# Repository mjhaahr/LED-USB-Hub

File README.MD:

# 3-Port USB Hub with Integrated Microcontroller and RGB USB-A ports

V1 uses the SL2.1a USB Hub
V2 will switch to a more full-featured USB Hub Controller and more closely comply with the USB Spec

Features:
- 3x RGB LED USB (USB A, 2.0 Speed) ports
- 1x USB C Port (downstream)
- 1x RP 2040
  - V1 used an Adafruit KB2040
  - V2 will switch to a standalone implementation
- Possibly exposed connectors for more features externally or internally (i.e. leaving a cutout in the board with room for expansion)

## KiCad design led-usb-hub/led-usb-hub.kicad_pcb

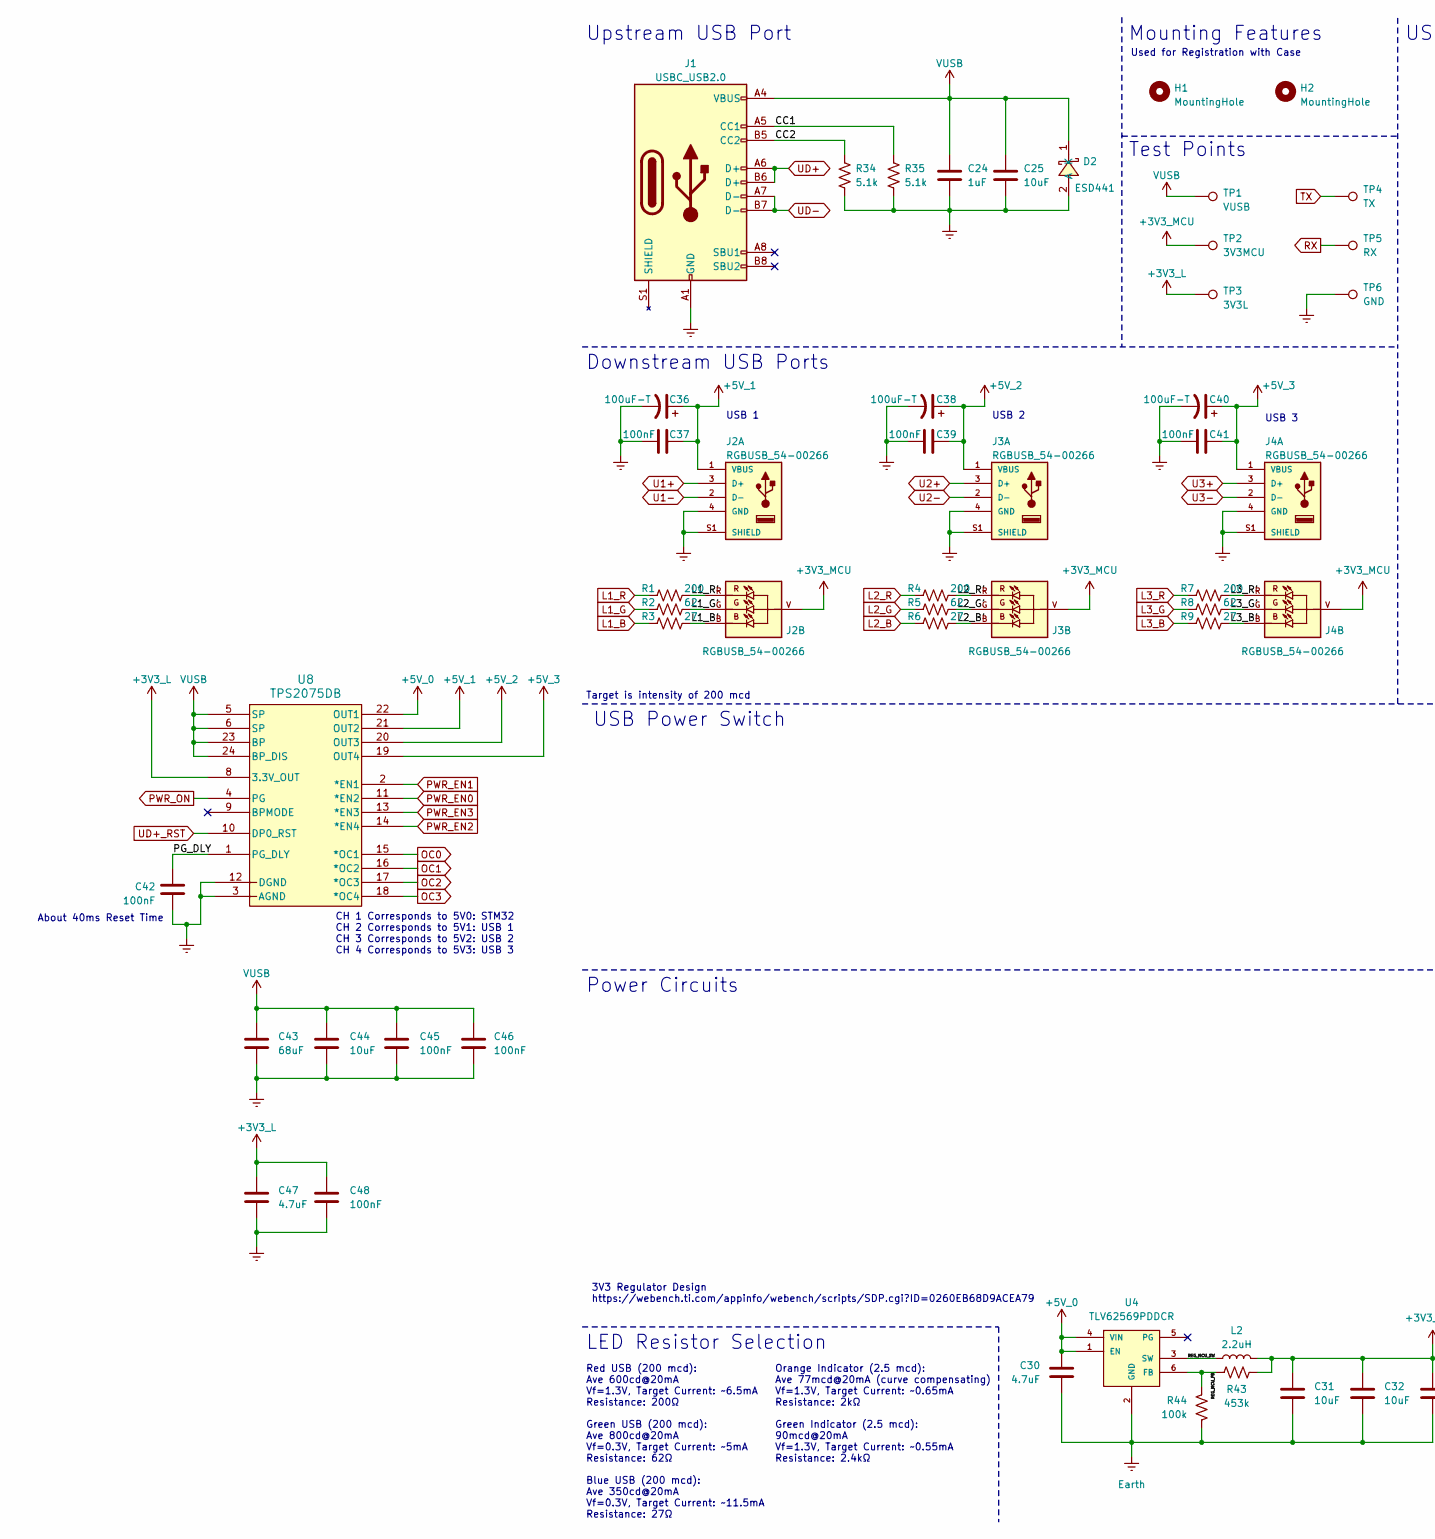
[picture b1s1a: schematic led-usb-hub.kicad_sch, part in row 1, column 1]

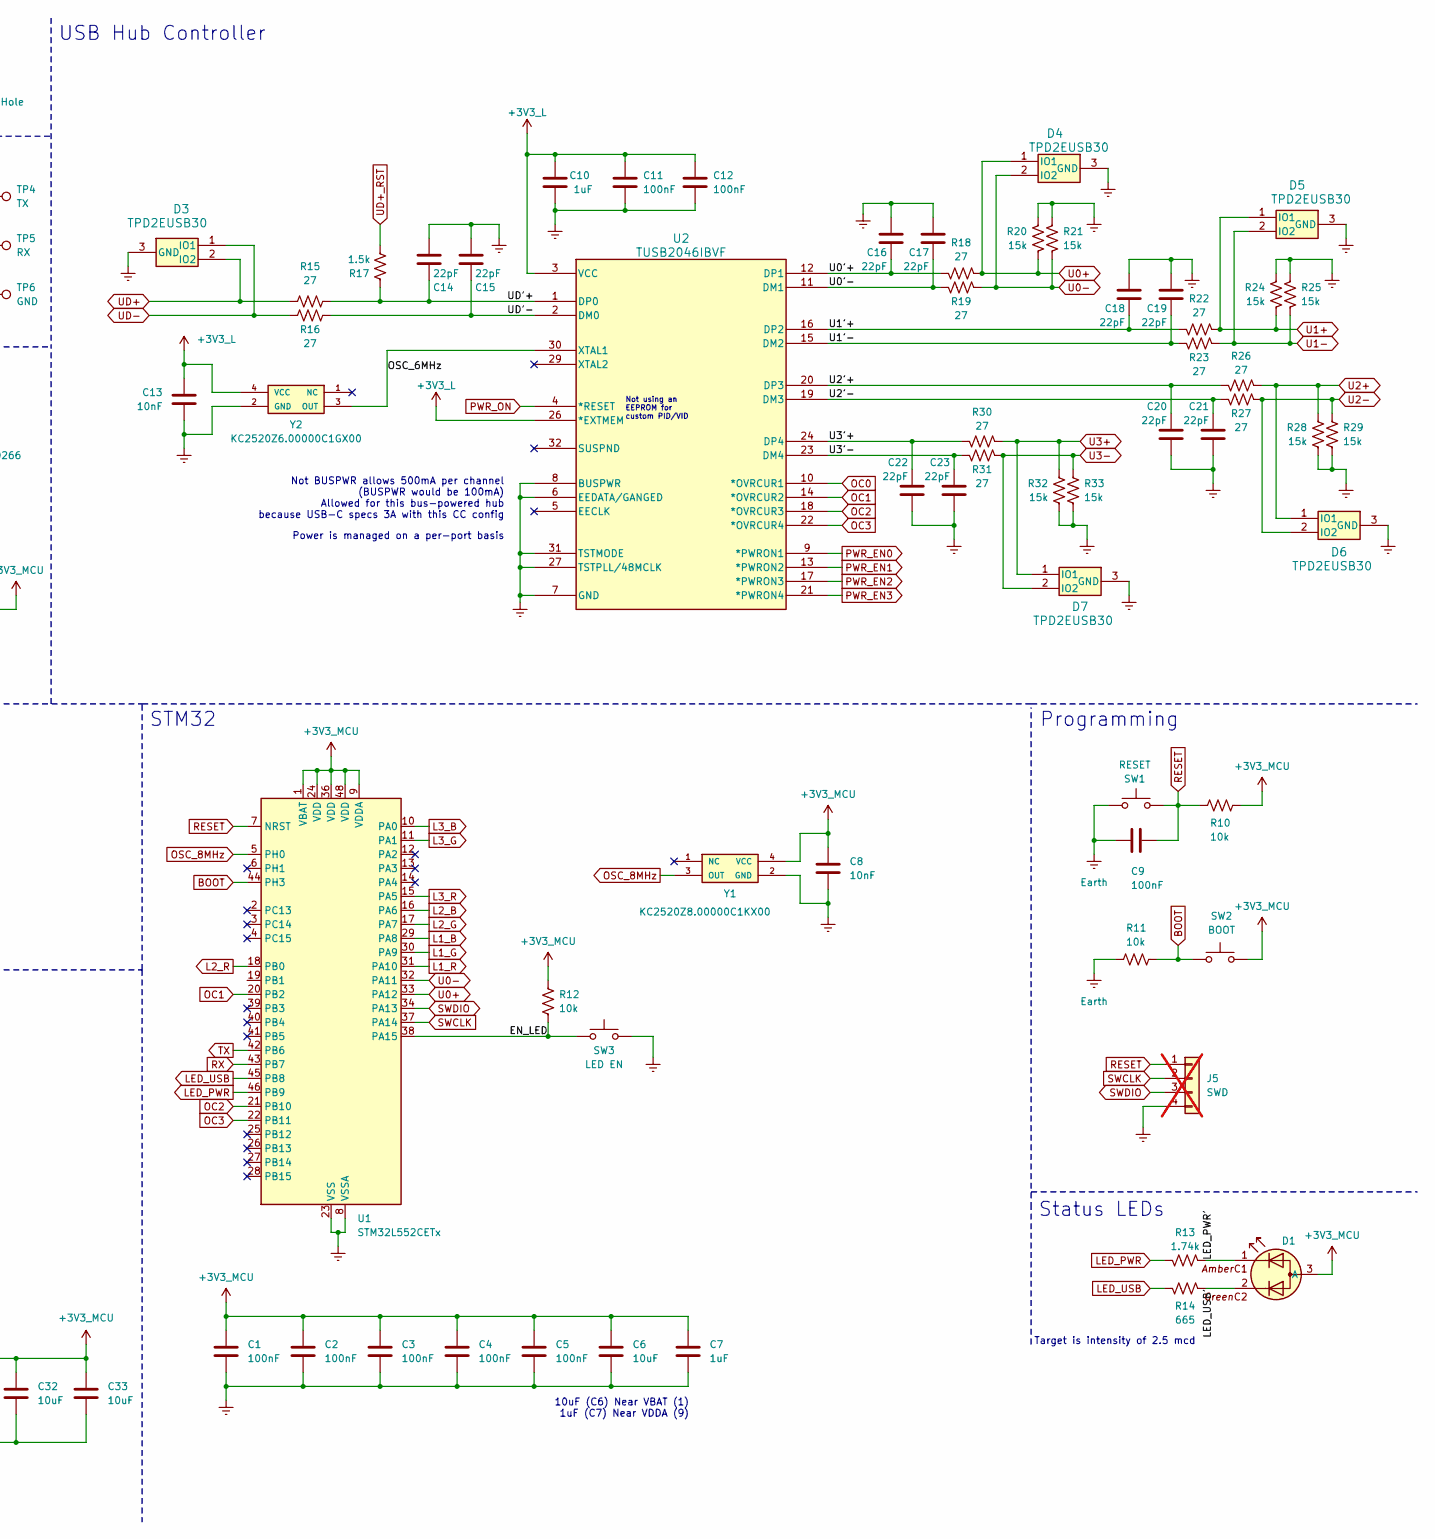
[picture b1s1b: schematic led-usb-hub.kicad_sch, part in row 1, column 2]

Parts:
C1, C2, C3, C4, C5, C9: 100nF; C_0603_1608Metric; LCSC Part C7472949
C6: 10uF; C_0603_1608Metric; LCSC Part C7472949
C7: 1uF; C_0603_1608Metric; LCSC Part C7472949
C8, C13: 10nF; C_0603_1608Metric; LCSC Part C7472949
C10, C24: 1uF; C_0603_1608Metric
C11, C12, C37, C39, C41, C42, C45, C46, C48: 100nF; C_0603_1608Metric
C14, C15, C16, C17, C18, C19, C20, C21, C22, C23: 22pF; C_0603_1608Metric
C25, C31, C32, C33, C44: 10uF; C_0603_1608Metric
C30, C47: 4.7uF; C_0603_1608Metric
C36, C38, C40: 100uF-T; CP_EIA-3528-15_AVX-H
C43: 68uF; C_0603_1608Metric
D1: HSMF-C143
D2: ESD441; X2SON-2_L0.6-W0.3-P0.35_ESD441DPLR; LCSC Part C22427765
D3, D4, D5, D6, D7: TPD2EUSB30; DRT0003A
H1, H2: MountingHole; MountingHole_2mm
J1: USBC_USB2.0; USB_C_Receptacle_GCT_USB4085
J2, J3, J4: RGBUSB_54-00266; PARTREV A; DigiKey_Part_Number 839-54-00266TR-ND
J5: SWD; PinHeader_1x04_P2.54mm_Vertical; not fitted
L2: 2.2uH; IND_SRP4020FA-2R2M_BRN
R1, R4, R7: 200; R_0603_1608Metric
R2, R5, R8: 62; R_0603_1608Metric
R3, R6, R9, R15, R16, R18, R19, R22, R23, R26, R27, R30, R31: 27; R_0603_1608Metric
R10, R11, R12: 10k; R_0603_1608Metric
R13: 1.74k; R_0603_1608Metric
R14: 665; R_0603_1608Metric
R17: 1.5k; R_0603_1608Metric
R20, R21, R24, R25, R28, R29, R32, R33: 15k; R_0603_1608Metric
R34, R35: 5.1k; R_0603_1608Metric
R43: 453k; R_0603_1608Metric
R44: 100k; R_0603_1608Metric
SW1: RESET; SW_EVQ-P7L01P
SW2: BOOT; SW_EVQ-P7L01P
SW3: LED EN; SW_EVQ-P7L01P
TP1: VUSB; TestPoint_Pad_1.0x1.0mm_Mod
TP2: 3V3MCU; TestPoint_Pad_1.0x1.0mm_Mod
TP3: 3V3L; TestPoint_Pad_1.0x1.0mm_Mod
TP4: TX; TestPoint_Pad_1.0x1.0mm_Mod
TP5: RX; TestPoint_Pad_1.0x1.0mm_Mod
TP6: GND; TestPoint_Pad_1.0x1.0mm_Mod
U1: STM32L552CETx; LQFP-48_7x7mm_P0.5mm
U2: TUSB2046IBVF; LQFP-32_7x7mm_P0.8mm
U4: TLV62569PDDCR; SOT95P280X110-6N
U8: TPS2075DB; SSOP-24_5.3x8.2mm_P0.65mm
Y1: KC2520Z8.00000C1KX00; OSC_KC2520Z8.00000C1KX00; PARTREV October 16, 2023
Y2: KC2520Z6.00000C1GX00; OSC_KC2520Z6.00000C1GX00; PARTREV October 16, 2023; DigiKey_Part_Number 478-KC2520Z6.00000C1GX00TR-ND

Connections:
+3V3_L: C10.1, C11.1, C12.1, C13.1, C47.1, C48.1, TP3.1, U2.3 (VCC), U2.25 (VCC), U2.26 (*EXTMEM), U8.8 (3.3V_OUT), Y2.4 (VCC)
+3V3_MCU: C1.1, C2.1, C3.1, C4.1, C5.1, C6.1, C7.1, C8.1, C31.1, C32.1, C33.1, D1.3 (A), J2.V, J3.V, J4.V, L2.2, R10.2, R12.1, R43.1, SW2.1, TP2.1, U1.1 (VBAT), U1.9 (VDDA), U1.24 (VDD), U1.36 (VDD), U1.48 (VDD), Y1.4 (VCC)
+5V_0: C30.1, U4.1 (EN), U4.4 (VIN), U8.22 (OUT1)
+5V_1: C36.1, C37.1, J2.1 (VBUS), U8.21 (OUT2)
+5V_2: C38.1, C39.1, J3.1 (VBUS), U8.20 (OUT3)
+5V_3: C40.1, C41.1, J4.1 (VBUS), U8.19 (OUT4)
/CC1: J1.A5 (CC1), R35.2
/CC2: J1.B5 (CC2), R34.2
/EN_LED: R12.2, SW3.1, U1.38 (PA15)
/L1_B': J2.B, R3.2
/L1_G': J2.G, R2.2
/L1_R': J2.R, R1.2
/L2_B': J3.B, R6.2
/L2_G': J3.G, R5.2
/L2_R': J3.R, R4.2
/L3_B': J4.B, R9.2
/L3_G': J4.G, R8.2
/L3_R': J4.R, R7.2
/LED_PWR': D1.1, R13.2
/LED_USB': D1.2, R14.2
/OSC_6MHz: U2.30 (XTAL1), Y2.3 (OUT)
/PG_DLY: C42.2, U8.1 (PG_DLY)
/REG_MCU_FB: R43.2, R44.2, U4.6 (FB)
/REG_MCU_SW: L2.1, U4.3 (SW)
/U0'+: C16.1, R18.1, U2.12 (DP1)
/U0'-: C17.1, R19.1, U2.11 (DM1)
/U1'+: C18.1, R22.1, U2.16 (DP2)
/U1'-: C19.1, R23.1, U2.15 (DM2)
/U2'+: C20.1, R26.1, U2.20 (DP3)
/U2'-: C21.1, R27.1, U2.19 (DM3)
/U3'+: C22.1, R30.1, U2.24 (DP4)
/U3'-: C23.1, R31.1, U2.23 (DM4)
/UD'+: C14.1, R15.1, R17.2, U2.1 (DP0)
/UD'-: C15.1, R16.1, U2.2 (DM0)
BOOT: R11.1, SW2.2, U1.44 (PH3)
Earth: C1.2, C2.2, C3.2, C4.2, C5.2, C6.2, C7.2, C8.2, C9.2, C10.2, C11.2, C12.2, C13.2, C14.2, C15.2, C16.2, C17.2, C18.2, C19.2, C20.2, C21.2, C22.2, C23.2, C24.2, C25.2, C30.2, C31.2, C32.2, C33.2, C36.2, C37.2, C38.2, C39.2, C40.2, C41.2, C42.1, C43.2, C44.2, C45.2, C46.2, C47.2, C48.2, D2.2 (A), D3.3 (GND), D4.3 (GND), D5.3 (GND), D6.3 (GND), D7.3 (GND), J1.A1 (GND), J1.A12 (GND), J1.B1 (GND), J1.B12 (GND), J2.4 (GND), J2.S1 (SHIELD), J2.S2 (SHIELD), J2.S3 (SHIELD), J2.S4 (SHIELD), J2.S5 (SHIELD), J3.4 (GND), J3.S1 (SHIELD), J3.S2 (SHIELD), J3.S3 (SHIELD), J3.S4 (SHIELD), J3.S5 (SHIELD), J4.4 (GND), J4.S1 (SHIELD), J4.S2 (SHIELD), J4.S3 (SHIELD), J4.S4 (SHIELD), J4.S5 (SHIELD), J5.4, R11.2, R20.2, R21.2, R24.2, R25.2, R28.2, R29.2, R32.2, R33.2, R34.1, R35.1, R44.1, SW1.2, SW3.2, TP6.1, U1.8 (VSSA), U1.23 (VSS), U1.35 (VSS), U1.47 (VSS), U2.6 (EEDATA/GANGED), U2.7 (GND), U2.8 (BUSPWR), U2.27 (TSTPLL/48MCLK), U2.28 (GND), U2.31 (TSTMODE), U4.2 (GND), U8.3 (AGND), U8.12 (DGND), Y1.2 (GND), Y2.2 (GND)
L1_B: R3.1, U1.29 (PA8)
L1_G: R2.1, U1.30 (PA9)
L1_R: R1.1, U1.31 (PA10)
L2_B: R6.1, U1.16 (PA6)
L2_G: R5.1, U1.17 (PA7)
L2_R: R4.1, U1.18 (PB0)
L3_B: R9.1, U1.10 (PA0)
L3_G: R8.1, U1.11 (PA1)
L3_R: R7.1, U1.15 (PA5)
LED_PWR: R13.1, U1.46 (PB9)
LED_USB: R14.1, U1.45 (PB8)
OC0: U2.10 (*OVRCUR1), U8.15 (*OC1)
OC1: U1.20 (PB2), U2.14 (*OVRCUR2), U8.16 (*OC2)
OC2: U1.21 (PB10), U2.18 (*OVRCUR3), U8.17 (*OC3)
OC3: U1.22 (PB11), U2.22 (*OVRCUR4), U8.18 (*OC4)
OSC_8MHz: U1.5 (PH0), Y1.3 (OUT)
PWR_EN0: U2.9 (*PWRON1), U8.11 (*EN2)
PWR_EN1: U2.13 (*PWRON2), U8.2 (*EN1)
PWR_EN2: U2.17 (*PWRON3), U8.14 (*EN4)
PWR_EN3: U2.21 (*PWRON4), U8.13 (*EN3)
PWR_ON: U2.4 (*RESET), U8.4 (PG)
RESET: C9.1, J5.1, R10.1, SW1.1, U1.7 (NRST)
RX: TP5.1, U1.43 (PB7)
SWCLK: J5.2, U1.37 (PA14)
SWDIO: J5.3, U1.34 (PA13)
TX: TP4.1, U1.42 (PB6)
U0+: D4.1 (IO1), R18.2, R20.1, U1.33 (PA12)
U0-: D4.2 (IO2), R19.2, R21.1, U1.32 (PA11)
U1+: D5.1 (IO1), J2.3 (D+), R22.2, R24.1
U1-: D5.2 (IO2), J2.2 (D-), R23.2, R25.1
U2+: D6.1 (IO1), J3.3 (D+), R26.2, R28.1
U2-: D6.2 (IO2), J3.2 (D-), R27.2, R29.1
U3+: D7.1 (IO1), J4.3 (D+), R30.2, R32.1
U3-: D7.2 (IO2), J4.2 (D-), R31.2, R33.1
UD+: D3.2 (IO2), J1.A6 (D+), J1.B6 (D+), R15.2
UD+_RST: R17.1, U8.10 (DP0_RST)
UD-: D3.1 (IO1), J1.A7 (D-), J1.B7 (D-), R16.2
VUSB: C24.1, C25.1, C43.1, C44.1, C45.1, C46.1, D2.1 (K), J1.A4 (VBUS), J1.A9 (VBUS), J1.B4 (VBUS), J1.B9 (VBUS), TP1.1, U8.5 (SP), U8.6 (SP), U8.23 (BP), U8.24 (BP_DIS)

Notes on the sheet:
USB 2
Not BUSPWR allows 500mA per channel (BUSPWR would be 100mA) Allowed for this bus-powered hub because USB-C specs 3A with this CC config
USB Hub Controller
LED Resistor Selection
Upstream USB Port
Target is intensity of 200 mcd
CH 1 Corresponds to 5V0: STM32 CH 2 Corresponds to 5V1: USB 1 CH 3 Corresponds to 5V2: USB 2 CH 4 Corresponds to 5V3: USB 3
STM32
Status LEDs
Blue USB (200 mcd): Ave 350cd@20mA Vf=0.3V, Target Current: ~11.5mA Resistance: 27Ω
Orange Indicator (2.5 mcd): Ave 77mcd@20mA (curve compensating) Vf=1.3V, Target Current: ~0.65mA Resistance: 2kΩ
USB Power Switch
Downstream USB Ports
Not using an EEPROM for custom PID/VID
3V3 Regulator Design https://webench.ti.com/appinfo/webench/scripts/SDP.cgi?ID=0260EB68D9ACEA79
Green USB (200 mcd): Ave 800cd@20mA Vf=0.3V, Target Current: ~5mA Resistance: 62Ω
About 40ms Reset Time
USB 3
Programming
USB 1
10uF (C6) Near VBAT (1) 1uF (C7) Near VDDA (9)
Test Points
Mounting Features
Target is intensity of 2.5 mcd
Power Circuits
Green Indicator (2.5 mcd): 90mcd@20mA Vf=1.3V, Target Current: ~0.55mA Resistance: 2.4kΩ
Power is managed on a per-port basis
Red USB (200 mcd): Ave 600cd@20mA Vf=1.3V, Target Current: ~6.5mA Resistance: 200Ω
Used for Registration with Case

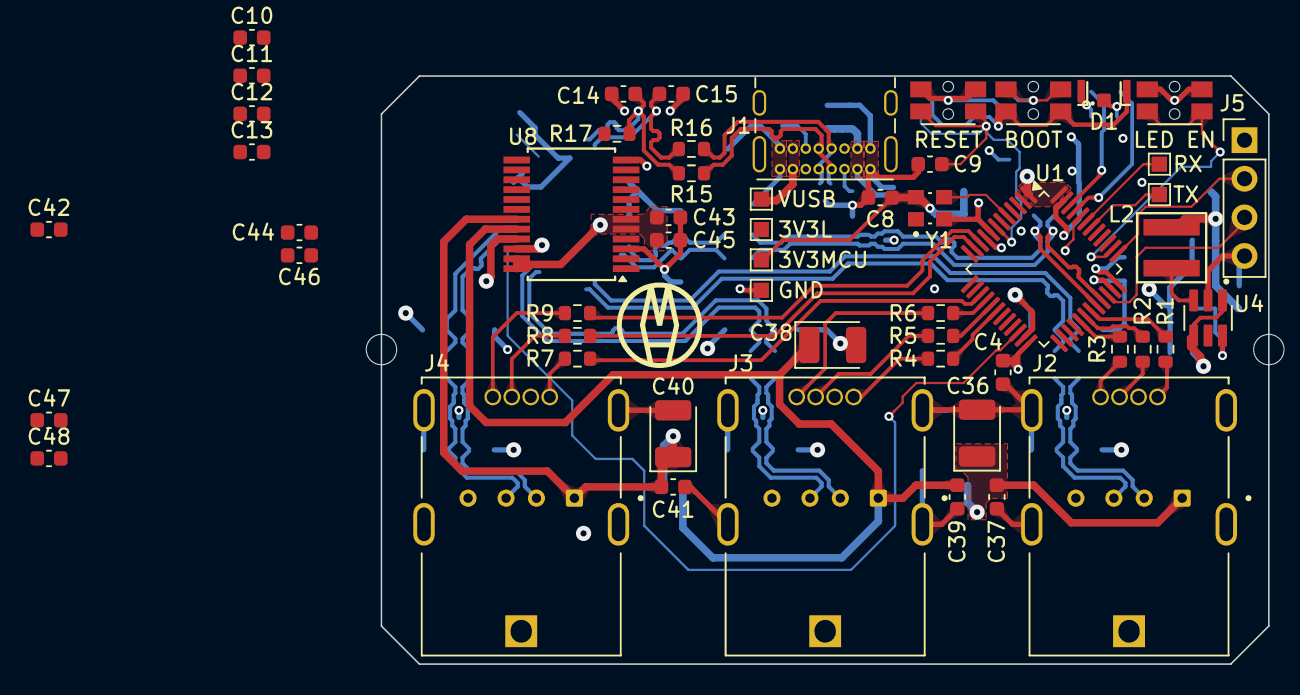
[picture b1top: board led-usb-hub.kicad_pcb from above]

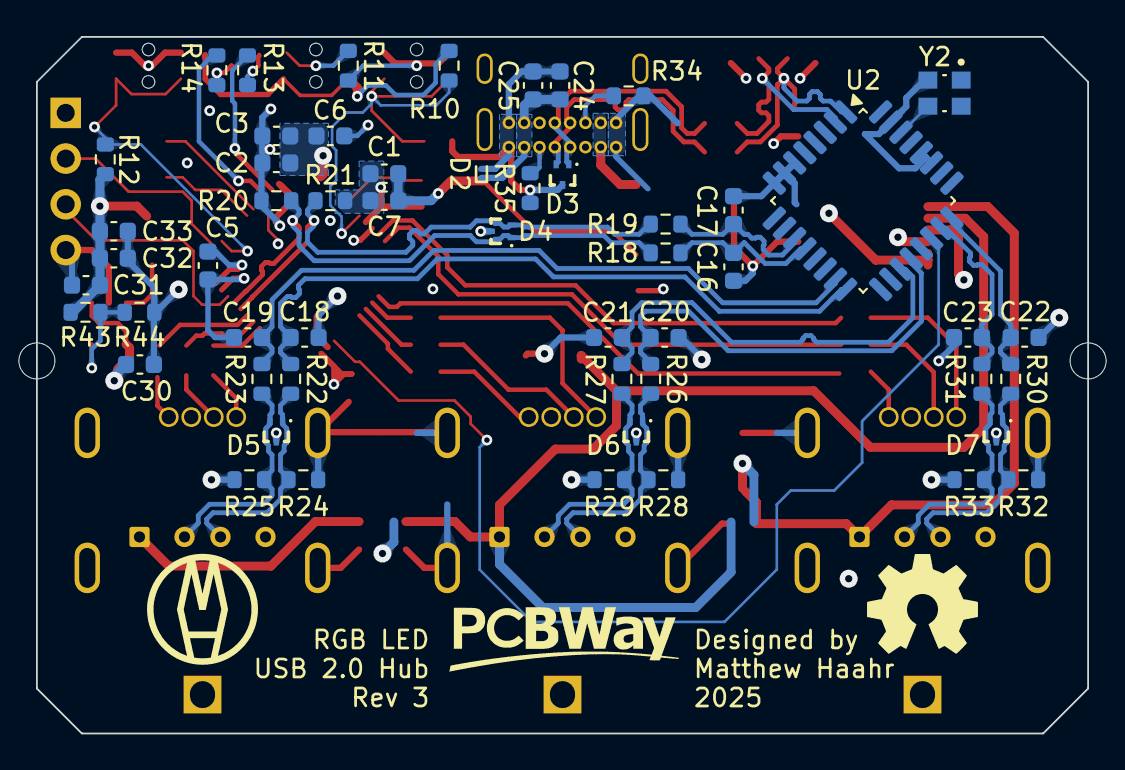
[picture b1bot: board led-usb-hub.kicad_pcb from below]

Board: 4 copper layers, 58.4 x 38.7 mm, 112 parts (55 on the bottom side), 74 nets.

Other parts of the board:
G1, G2, G3: LOGO

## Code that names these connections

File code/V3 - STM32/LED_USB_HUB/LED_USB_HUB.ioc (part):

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Mcu.Name=STM32L552C(C-E)Tx
Mcu.Package=LQFP48
Mcu.UserName=STM32L552CETx
PA1.GPIOParameters=GPIO_Label
PA1.GPIO_Label=USB3_BLUE
PA1.Signal=S_TIM2_CH2
PA10.GPIOParameters=GPIO_Label
PA10.GPIO_Label=USB1_RED
PA10.Signal=S_TIM1_CH3
PA11.Mode=Device
PA11.Signal=USB_DM
PA12.Mode=Device
PA12.Signal=USB_DP
PA13\ (JTMS/SWDIO).GPIOParameters=GPIO_Label
PA13\ (JTMS/SWDIO).GPIO_Label=SWDIO
PA13\ (JTMS/SWDIO).Mode=Serial_Wire
PA13\ (JTMS/SWDIO).Signal=DEBUG_JTMS-SWDIO
PA14\ (JTCK/SWCLK).GPIOParameters=GPIO_Label
PA14\ (JTCK/SWCLK).GPIO_Label=SWCLK
PA14\ (JTCK/SWCLK).Mode=Serial_Wire
PA14\ (JTCK/SWCLK).Signal=DEBUG_JTCK-SWCLK
PA15\ (JTDI).GPIOParameters=GPIO_Label
PA15\ (JTDI).GPIO_Label=LED_EN_BUTTON
PA15\ (JTDI).Signal=GPIO_Input
PA2.GPIOParameters=GPIO_Label
PA2.GPIO_Label=USB3_GREEN
PA2.Signal=S_TIM2_CH3
PA5.GPIOParameters=GPIO_Label
PA5.GPIO_Label=USB3_RED
PA5.Signal=S_TIM2_CH1
PA6.GPIOParameters=GPIO_Label
PA6.GPIO_Label=USB2_BLUE
PA6.Signal=S_TIM3_CH1
PA7.GPIOParameters=GPIO_Label
PA7.GPIO_Label=USB2_GREEN
PA7.Signal=S_TIM3_CH2
PA8.GPIOParameters=GPIO_Label
PA8.GPIO_Label=USB1_BLUE
PA8.Signal=S_TIM1_CH1
PA9.GPIOParameters=GPIO_Label
PA9.GPIO_Label=USB1_GREEN
PA9.Signal=S_TIM1_CH2
PB0.GPIOParameters=GPIO_Label
PB0.GPIO_Label=USB2_RED
PB0.Signal=S_TIM3_CH3
PB10.GPIOParameters=GPIO_Label
PB10.GPIO_Label=USB2_OC
PB10.Signal=GPIO_Input
PB11.GPIOParameters=GPIO_Label
PB11.GPIO_Label=USB3_OC
PB11.Signal=GPIO_Input
PB2.GPIOParameters=GPIO_Label
PB2.GPIO_Label=USB1_OC
PB2.Signal=GPIO_Input
PB6.Mode=Asynchronous
PB6.Signal=USART1_TX
PB7.Mode=Asynchronous
PB7.Signal=USART1_RX
PB8.GPIOParameters=PinState,GPIO_Label
PB8.GPIO_Label=LED_USB
PB8.PinState=GPIO_PIN_SET
PB8.Signal=GPIO_Output
PB9.GPIOParameters=PinState,GPIO_Label
PB9.GPIO_Label=LED_PWR
PB9.PinState=GPIO_PIN_SET
PB9.Signal=GPIO_Output
PH0-OSC_IN\ (PH0).GPIOParameters=GPIO_Label
PH0-OSC_IN\ (PH0).GPIO_Label=HSI_IN
PH0-OSC_IN\ (PH0).Mode=HSE-External-Oscillator
PH0-OSC_IN\ (PH0).Signal=RCC_OSC_IN
PH1-OSC_OUT\ (PH1).GPIOParameters=GPIO_Label
PH1-OSC_OUT\ (PH1).GPIO_Label=HSI_OUT
PH1-OSC_OUT\ (PH1).Mode=HSE-External-Oscillator
PH1-OSC_OUT\ (PH1).Signal=RCC_OSC_OUT
PH3-BOOT0.GPIOParameters=GPIO_Label
PH3-BOOT0.GPIO_Label=BOOT_BUTTON
PH3-BOOT0.Signal=GPIO_Input
RCC.HSE_VALUE=8000000
RCC.SYSCLKFreq_VALUE=32000000
RCC.SYSCLKSource=RCC_SYSCLKSOURCE_PLLCLK
board=custom

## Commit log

2023-07-10 Initial Commit, Creating Repo
2023-07-10 Add README
2023-07-12 Start Schematic USB Controller and USB-C Upstream Added
2023-07-20 Added USB ports
2023-08-01 Finish Schematic V1
2023-08-01 Create Footprints
2023-08-02 Start LAyout
2023-08-02 Cont Routing, better layout
2023-08-03 Cont Routing Need: Osc, Switch, USB port (check part inventory for all Design switch action before commiting design
2023-08-04 Cont routing Need footprints for SW and Osc Need mounting holes in corners
2023-08-06 finish routing NEED: graphics and labels
2023-08-07 Add holes and graphics Tune trace length
2023-08-10 Add indicator LEDs
2023-08-11 Finalized and Ordered
2023-08-17 Update footprints after board arrived
2023-08-24 Updates for readability and cleanliness
2023-12-26 A bit of clean up
2023-12-27 Update Schematic: Start Switch to new TI parts Add USB Power Switches Clean Up
2023-12-27 Fix file name
2023-12-27 Add USB Parts TODO: Crystals (6 MHz for USB cont 12 MHz for Pi) TODO: RP2040 Stuff (caps, buttons for boot and reset, flash) TODO: Wire up LEDs (and add PWR and USB data present LEDs) Maybe TODO: add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
2023-12-27 Remove TODO: BUSPWR is fine b/c USB-C is a 15W spec
2023-12-27 Add Caps for RP2040 and correct values (caps, series and pullup resistors TODO: Crystals TODO: Bootsel and Reset Buttons TODO: Flash TODO: LEDs for PWR and USB Link Maybe TODO: internal connectors
2023-12-27 Swap ESD Diode to larger package Add missing resistors to Power Circuits Assign footprints to most components TODO: Footprints for inductors and tantalum caps (pick parts) TODO: 3D Models for USB Por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
2023-12-27 Add Reset Power On Chip Holds Reset Low (in Reset state) for 200 us while clock starts to allow logic to be enabled on the USB controller
2023-12-27 Update USB Port Models to Official ones
2023-12-28 Add Crystals and fix USB models TODOS: Status LEDs TODO: Buttons (RST,BOOTSEL,LEDs) TODO: Flash Chip TODO: Spec Inductors and Tantalum Caps (see TUSB and TPS docs)
2023-12-28 Update README.md
    Add Flash Chip
2023-12-28 Add Boot Flash, SWD Header, and Reset and BOOTSEL Buttons TODO: Spec Inductors and Tantalum Caps (see TUSB and TPS docs) TODO: Status LEDs TODO: LED Enable Button TODO: spec buttons and model them
2023-12-28 Add LEDs to schematic For LED function: make button cycle between ports and status, just ports, all off TODO: Pick LEDs and find resistor values for that (orange and green) TODO: spec inductors and t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
2023-12-28 Update README.md
    Add more docs to README
2023-12-28 Rearrange schematic
2023-12-29 Spec LEDs TODO: Footprints and models for KSS221 Switches TODO: spec inductors and tantalum caps Then layout (but also find all the rest of the passives necessary, some sizes may change)
2023-12-29 Update README.md
    Added LEDs
    Still missing Caps, Resistors, and Inductors
2023-12-29 Add Footprints and models for switches TODO: Spec all passives to finalize footprints (if staying at 0603) TODO: Find Inductor and C-T footprints Then it's layout
2023-12-29 Unify values a bit
2023-12-29 Remove model of SWD pins, show as unpopulated
2023-12-29 Update README.md
    Add Resistor, Capacitor, and Inductor Values
2023-12-30 All Components have first pass footprints, need to go through all passives to verify
2023-12-30 Fit Crystal Series Resistor value better
2023-12-30 Update README.md
    All components verified
2023-12-30 Upload images for embedding (schematic and psu)
2023-12-30 actually upload psu
2023-12-30 Update README.md
    Add images to README
2023-12-30 Add 0.1uF decoupling caps for USB Power Switches, rec by TI
2023-12-30 Start layout ideas, mostly just figure out where components will go
2023-12-30 Update README.md
    Switch datasheets from vendor-hosted to manufacturer-hosted and link Digi-Key cart
2023-12-30 Switch TVS diode for one that's easier to route Figure out how to route diff traces
2023-12-31 Fix decoupling cap count and start component arrangement
2023-12-31 Update images to back with white
2023-12-31 Flip USB Hub Controller for better routing, continue placing components swap sizes of 0603 to not hand soldering
2023-12-31 More component placing
2024-01-01 Finalize some component placement and route all differential traces (may end up condensing later)
2024-01-01 Continue rotuing and component placing: Still TODO: RP2040 (basically everything, but USB) QSPI Flash 12 MHz osc LED Traces OC and PWR lines for USB PWR and the pullups Buttons Mounting Holes
2024-01-01 Cont rotuing, add mounting holes, do RP2040 Still todo: Power Control PWR and OC lines and associated pullups USB Port RGB lines, and the 3v3 line for that as well (make a trunk line under) DRC passi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
2024-01-02 Finish routing, need some verification and checking to ensure that it's good before I order
2024-01-02 Increase minimum via size Update and clean up
2024-01-03 Fix angles on board edges
2024-01-12 Add Logo and OSHW Mark
2024-01-12 Add descriptive text TODO: see if I can shorten the board
2024-01-13 Start Shortening, moved RP2040 as far -Y as possible, need to do the USB ports and LED lines
2024-01-13 More shortening, need to move the USB Ports, will add zig-zags, also think about moving the USB Controller
2024-01-14 More shortening, probably will do another pass of this, but the central usb port will be a challenge
2024-01-15 More Shrinkage TODO: More TODO: Nice Lables
2024-01-15 Prempt moving the USB IC by moving the USB Upstream Traces, can probably shift the whole board about 0.2 in total
2024-01-15 USB IC Moved, may be able to get it some more, but not gonna try right now TOOD: More the USB Ports Now
2024-01-15 Move USB Lines up some
2024-01-16 Finish shrink TODO: Fancy Labels TODO: Test Points
2024-01-16 Fix some labels and mechanical sizes
2024-01-16 Update models with better colors Export First Pass Step File for making a case
2024-01-17 Update Board to use #6 Screws
2024-01-17 Beautification
2024-01-17 More beautification
2024-01-17 Clean up pad traces with zones
2024-01-17 Add Teardrops
2024-01-18 Fix Values for LED Resistors, add Test Points
2024-01-18 More clean up
2024-01-18 Update documentation with current designs and continue clean up
2024-01-18 Clean up labels
2024-01-18 Clean up some labels
2024-01-18 Remove track through GND layer MAYBE TODO: swap crystals for a smaller package, condense the routing a bit
2024-01-18 Set Net Colors
2024-01-19 Update Schematic Labels
2024-01-19 Clean up schematic a little bit and switch to using correct power symbols
2024-01-19 Clean up schematic to label directions
2024-01-19 Clean up, clean up, everybody everywhere
2024-01-20 Use Net Classes Properly and lots of clean up
2024-01-21 Clean up traces and zones (specifically grounds
2024-01-21 Clean up, label all nets
2024-01-21 More clean up, better pin assignment for decoupling
2024-01-21 Even more goddamn clean up and closer placement of decoupling caps
2024-01-21 Add Case Design and future implementation notes
2024-01-22 Clean up and aligning
2024-01-22 Correct Annular Ring Sizes
2024-01-31 Larger inductor traces
2024-02-03 More zoning
2024-02-19 Pick better LED resistor values
2024-02-19 Fix dangling note
2024-02-19 Switch 'Brightness' to 'Intensity', more technically correct
2024-02-19 Final pass on components and layout V2 Ordering will happen soon
2024-02-19 Add Stitching Vias Generate Gerbers
2024-02-19 Compress Gerbers for Upload
2024-02-19 Whoops, forgot to re-add the Teardrops
2024-02-19 Update USB differential traces to match with the specifcations from JLC PCB (switch from PCBWay for pricing)
2024-02-20 Typos
2024-02-20 Update Render of board with current design
2024-02-20 Add case Files
2024-02-20 Fix link
2024-02-20 Fix Do Not Fit Resistor
2024-02-20 Update Bom and DNP mark
2024-02-20 Clear up DNP Note
2024-02-20 Ignore Circuit Python Build
2024-02-20 First CircuitPython Build
2024-02-21 Improve case design for real screw size
2024-02-21 Fix hole size in PCB
2024-02-28 Update routing for 4mm screw hole Improve bom file (properly drop DNP, Test Points, and Holes
2024-03-02 Updated CircuitPython Config, it works
2024-03-02 IT WORKS TODO: still need to get the LED_EN button working, but prototype works
2024-03-03 LEDs now cycle Also no-longer acts as a remove-able flash drive unless button is held
2024-03-03 Update README.md with Code info
2024-03-03 Update Boot.Py to prevent keyboard prompting, in theory Also tracking in script to remount the device, because sometimes editing Boot.Py breaks
2024-03-05 Remove Power-On Monitor, was causing issues with device booting Switch to using a MAX809T for future revisions
2024-03-05 Fix POR Chip, I hope, to be tested when it arrives
2024-03-07 Improving boot code
2024-03-07 More tuning of RGB Params
2024-03-08 Tuning LED Params
2024-03-08 Update BOM and clean up more
2024-03-08 remove boot prints
2024-03-08 Update README.md
    Ad TOC
2025-03-11 Upload New Header Image
2025-03-11 Update README.md
    Include new image
2025-05-21 Update README.md
    Add more future improvements
2025-05-21 [HW] Switch 3V3 Reg to AMS1117 Varaint (Maybe for a PCBWay Sponsorship)
2025-05-22 [HW] Switch to RP2354 and start stripping down
2025-06-07 [HW] Continue updating layout Route USB Traces Route LED Traces TODO: Finalize MCU, Oscillators, 3V3 Regs
2025-06-07 [HW] Continue updated layout
2025-06-07 [HW] Improve Routing and Diff Tune Params TODO: Finalize MCU choice (STM32 likely) TODO: Finalize 3V3 Regs (AMS1117 or something better) TODO: Pick new Oscillators TODO: SWD Conn Mod (NRST) (or 10 pi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
2025-06-08 [HW] Pick MCU (STM32L552 48 pin LQFP) TODO: Oscillators TODO: 3V3 REGs TODO: Test Points (3 Voltages (VUSB, 3V3L, 3V3MCU), GND, TX/RX, PWR ON) TODO: Silks (Logos, Names, etc...) TODO: Screw Holes (do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
2025-06-08 [HW] Add Oscillaotrs and Test Points TODO: 3V3 Regs TODO: Silks (Logos, Names, etc...) TODO: Screw Holes (smaller than M3, those are huge) TODO: BOOT0 (and DFU HW Config)
2025-06-08 [HW] 3V3 Regs TODO: Re-annotate Board TODO: TVS Diode for USB TODO: Silks (Logos, Names, etc...) TODO: Screw Holes (smaller than M3, those are huge) TODO: BOOT0 (and DFU HW Config)
2025-06-08 [HW] Add Silks and USB TVS Diode TODO: Re-annotate TODO: BOOT0 Switch to enable DFU TODO: Add SWD Connector (include NRST) TODO: Mounting Options
2025-06-08 [HW] Added Boot SW (for DFU Mode, and swapped to smaller switches), Added SWD Connector, Swapped to smaller Inductors TODO: Re-annotate by group TODO: Mounting
2025-06-09 [HW] Match constraints to PCBWay
2025-06-09 [HW] Reannotate board TODO: Mounting holes? TODO: Update Readme
2025-06-09 [HW] Added MAX809 PWR Supervisor IC and jumper in case PG from Reg isn't good enough
2025-06-10 [HW] Fix ESD Diode placement
2025-06-10 [HW] Trace Clean up
2025-06-13 [HW] Remove Mounting Holes TODO: Move USB Ports/Board Edges Around to get connectors with correct stickout (1.2mm?)
2025-06-13 [HW] Rearrange to allow port hangover board edge (better for case) TODO: Figure out mounting/alignment Case might provide all mounting and just need registration So could add semi-circles on board ed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
2025-06-13 [HW] Add mounting/registration points, export Fab tools
2025-06-13 [HW] More Space
2025-06-16 [HW] Update BOM and Docs
2025-06-16 [HW] Switch LED to side-firing bi-color LED
2025-06-16 [Docs] Add PCBWay Sponsorship notice and sned them board files
2025-06-17 [HW] Order Parts and Boards
2025-06-18 [SW] Setup PWM Timers (maybe correctly, need to check with logic analyzer (for freq and polarity)
2025-06-23 [SW] Setup CubeIDE
2025-06-25 [SW] First Pass at code Not Working, need debugger
2025-06-25 [SW] Actually add the files this time
2025-06-26 [Docs] PCBWay Sponsor Copy and Board Images
2025-06-26 Update README.md
    More sponsor-copy
2025-06-26 [SW] Maybe get the LEDs working (first the pointer things)
2025-06-26 [HW] Add TPS2075 for better Reset Logic
2025-06-26 [HW]Re-arrange schematic
